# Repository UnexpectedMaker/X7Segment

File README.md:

# X7Segment Display
X7 Segment displays are RGB LED based 7 Segment boards that you can chain together and control via any micro-controller just like you would control a strip of RGB LEDs. They just require VCC, GND and Data from a GPIO.

You can purchase these displays pre-built on [tindie](https://www.tindie.com/products/16900/)

I have released this project as open source, so if you would like you make your own for personal use, you can download the CAD files from this repo.

The hardware has been released as open source under the CERN license. Please review the license before using these files in your own projects to understand your obligations.

The software has been released as open source under the MIT license. Please review the license before using these files in your own projects to understand your obligations.

# X7Segment Display Library
An API that lets you display numbers and letters on X7Segment RGB LED displays that are available from [tindie](https://www.tindie.com/products/16900/)

You can find the Open Source hardware PCB design and Gerber files [here](https://github.com/UnexpectedMaker/X7Segment/CAD)

# Support Unexpected Maker

I love designing, making and releasing our projects as open source. I do it because I believe it’s important to share knowledge and give back to the community, like many have done before me. It helps us all learn and grow.

That said, a lot of time, effort and finances have gone into designing and releasing these files, so please consider supporting me by buy some of my TiinyPICO products:

https://tinypico.com/shop

Or by buying one of our products on tindie:

https://www.tindie.com/stores/seonr/

Or by becoming a Patron:

https://www.patreon.com/unexpectedmaker

# Unexpected Maker
http://youtube.com/c/unexpectedmaker

http://twitter.com/unexpectedmaker

https://www.facebook.com/unexpectedmaker/

https://www.instagram.com/unexpectedmaker/

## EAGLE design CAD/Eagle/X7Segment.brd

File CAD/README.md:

# X7Segment Display
X7 Segment displays are RGB LED based 7 Segment boards that you can chain together and control via any micro-controller just like you would control a strip of RGB LEDs. They just require VCC, GND and Data from a GPIO.

You can purchase these displays pre-built on [tindie](https://www.tindie.com/products/16900/)

I have released this project as open source, so if you would like you make your own for personal use, you can download the CAD files from this repo.

This hardware has been released as open source under the CERN license. Please review the license before using these files in your own projects to understand your obligations.

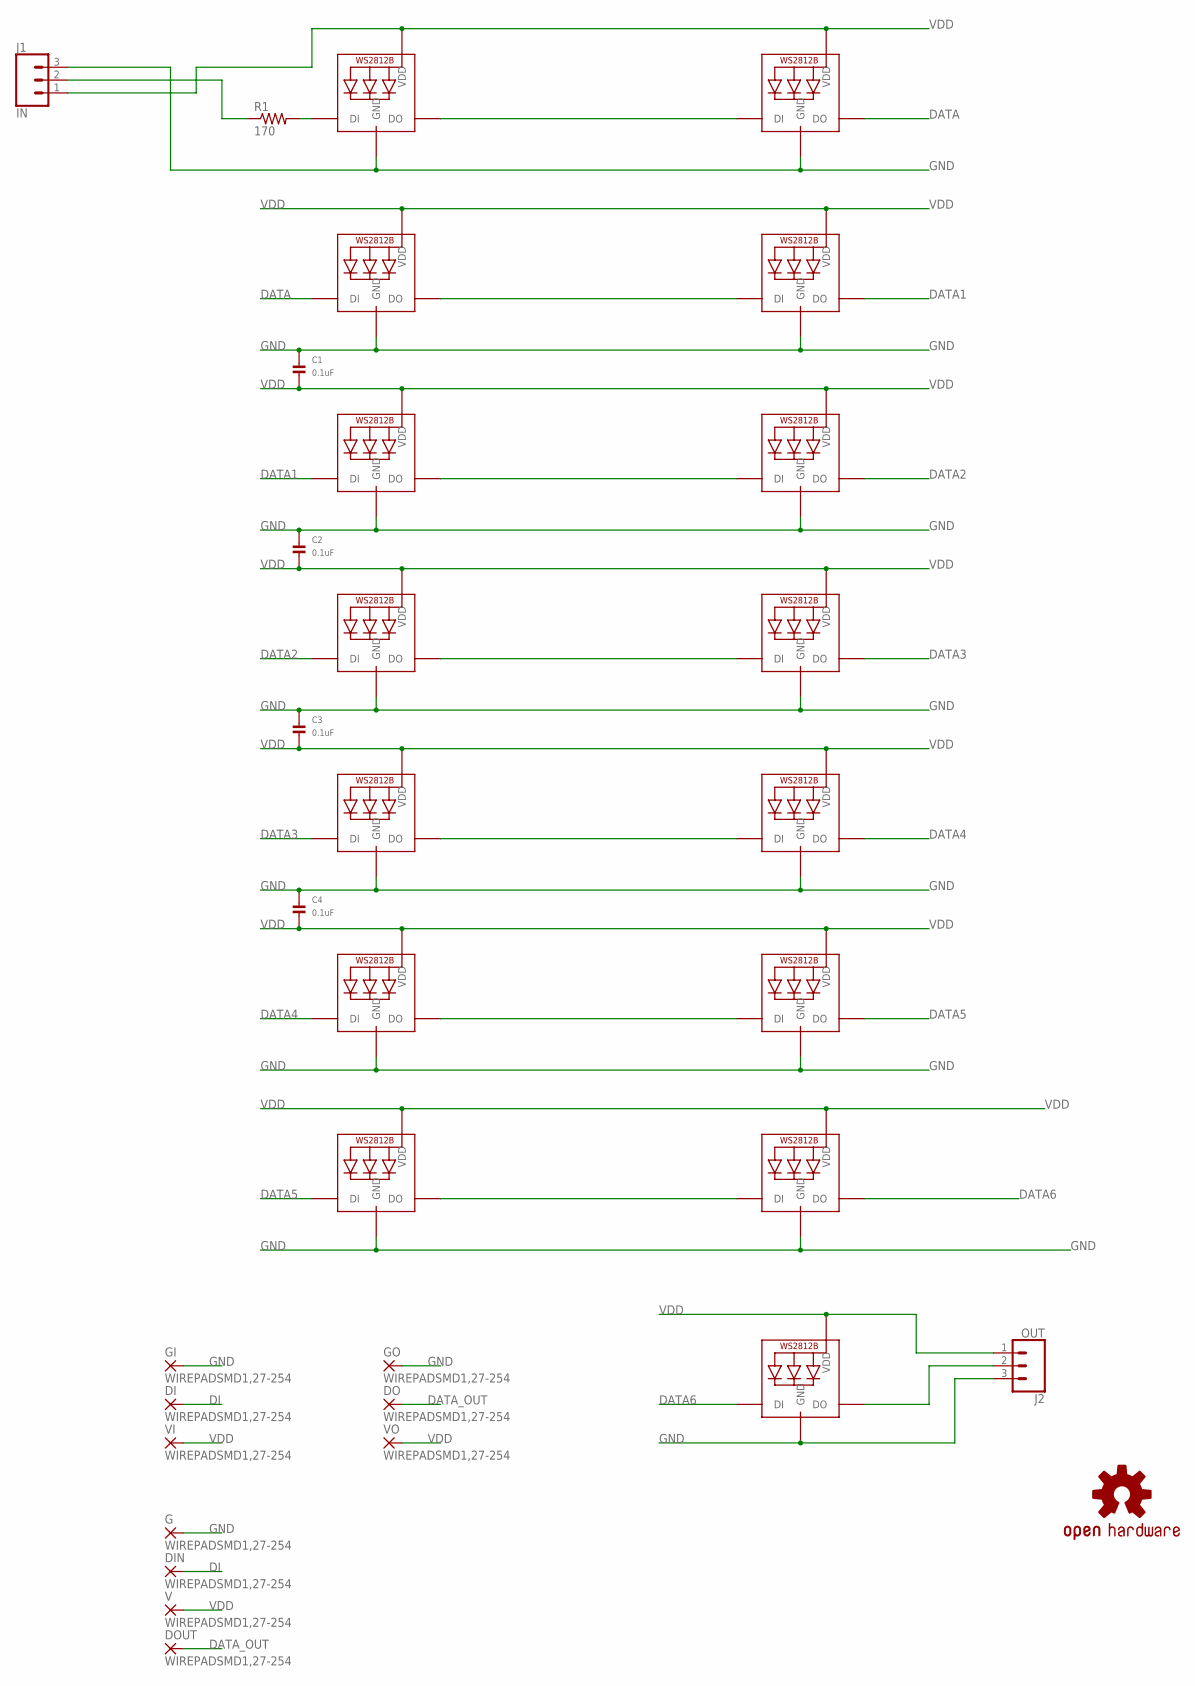
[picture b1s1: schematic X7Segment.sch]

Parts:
C1, C2, C3, C4: 0.1uF; _0603MP
DI: WIREPADSMD1,27-254; SMD1,27-2,54
DIN: WIREPADSMD1,27-254; SMD1,27-2,54
DO: WIREPADSMD1,27-254; SMD1,27-2,54
DOUT: WIREPADSMD1,27-254; SMD1,27-2,54
G: WIREPADSMD1,27-254; SMD1,27-2,54
GI: WIREPADSMD1,27-254; SMD1,27-2,54
GO: WIREPADSMD1,27-254; SMD1,27-2,54
J1: IN; 1X03_NO_SILK
J2: OUT; 1X03_NO_SILK
LED1, LED4, LED5, LED8, LED9, LED12, LED13, LED16, LED17, LED20, LED21, LED24, LED25, LED28: WS2812B4020_SIDEWAYS; 4020_SIDEWAYS
LED29: RGB 3535; LED3535
LOGO1: OSHW-LOGOS; OSHW-LOGO-S
R1: 170; R0805
V: WIREPADSMD1,27-254; SMD1,27-2,54
VI: WIREPADSMD1,27-254; SMD1,27-2,54
VO: WIREPADSMD1,27-254; SMD1,27-2,54

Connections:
DATA: LED4.2-DOUT (DO), LED5.4-DIN (DI)
DATA1: LED8.2-DOUT (DO), LED9.4-DIN (DI)
DATA2: LED12.2-DOUT (DO), LED13.4-DIN (DI)
DATA3: LED16.2-DOUT (DO), LED17.4-DIN (DI)
DATA4: LED20.2-DOUT (DO), LED21.4-DIN (DI)
DATA5: LED24.2-DOUT (DO), LED25.4-DIN (DI)
DATA6: LED28.2-DOUT (DO), LED29.1 (DI)
DATA_OUT: DO.1, DOUT.1, J2.2, LED29.3 (DO)
DI: DI.1, DIN.1, J1.2, R1.1
DI_R: LED1.4-DIN (DI), R1.2
GND: C1.1, C2.1, C3.1, C4.1, G.1, GI.1, GO.1, J1.3, J2.3, LED1.3-GND (GND), LED4.3-GND (GND), LED5.3-GND (GND), LED8.3-GND (GND), LED9.3-GND (GND), LED12.3-GND (GND), LED13.3-GND (GND), LED16.3-GND (GND), LED17.3-GND (GND), LED20.3-GND (GND), LED21.3-GND (GND), LED24.3-GND (GND), LED25.3-GND (GND), LED28.3-GND (GND), LED29.4 (GND)
unnamed: LED5.2-DOUT (DO), LED8.4-DIN (DI)
unnamed: LED9.2-DOUT (DO), LED12.4-DIN (DI)
unnamed: LED13.2-DOUT (DO), LED16.4-DIN (DI)
unnamed: LED21.2-DOUT (DO), LED24.4-DIN (DI)
unnamed: LED25.2-DOUT (DO), LED28.4-DIN (DI)
unnamed: LED1.2-DOUT (DO), LED4.4-DIN (DI)
unnamed: LED17.2-DOUT (DO), LED20.4-DIN (DI)
VDD: C1.2, C2.2, C3.2, C4.2, J1.1, J2.1, LED1.1-VDD (VDD), LED4.1-VDD (VDD), LED5.1-VDD (VDD), LED8.1-VDD (VDD), LED9.1-VDD (VDD), LED12.1-VDD (VDD), LED13.1-VDD (VDD), LED16.1-VDD (VDD), LED17.1-VDD (VDD), LED20.1-VDD (VDD), LED21.1-VDD (VDD), LED24.1-VDD (VDD), LED25.1-VDD (VDD), LED28.1-VDD (VDD), LED29.2 (VDD), V.1, VI.1, VO.1

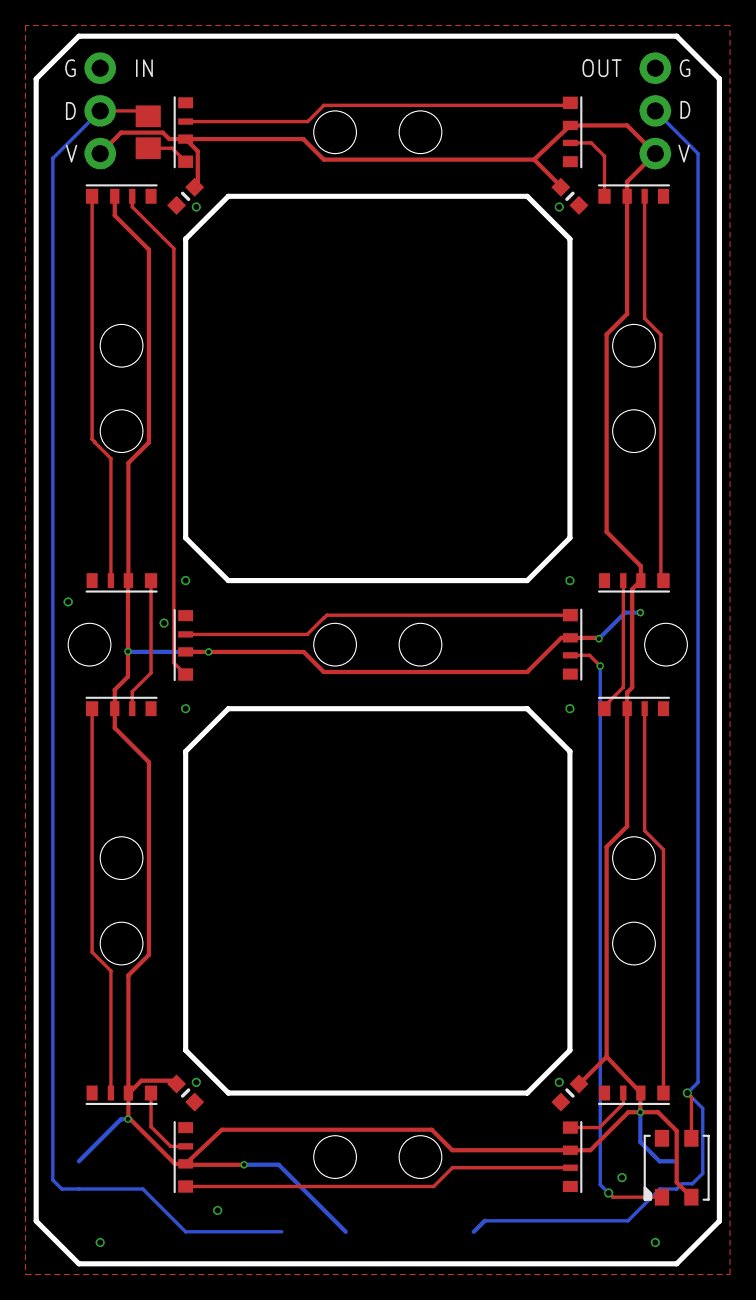
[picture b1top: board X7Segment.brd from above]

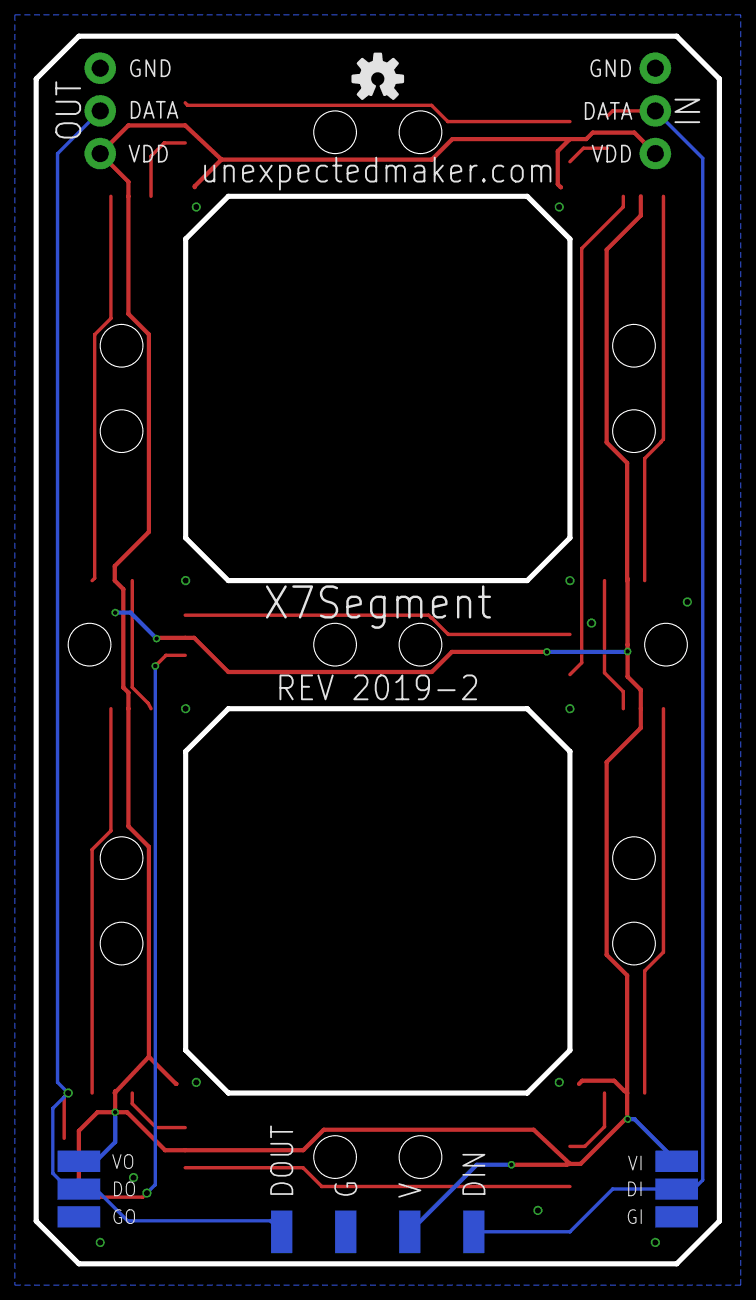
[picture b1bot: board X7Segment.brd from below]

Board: 2 copper layers, 40.6 x 73.0 mm, 33 parts (11 on the bottom side), 19 nets.

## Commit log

2019-12-26 Initial commit of Arduino library and design files

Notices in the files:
parts and their libraries:
SparkFun-Connectors: Licensing: Creative Commons ShareAlike 4.0 International - https://creativecommons.org/licenses/by-sa/4.0
microbuilder: This work is placed in the public domain, and may be freely used for commercial and non-commercial work with the following conditions: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
